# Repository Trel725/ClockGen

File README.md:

# ClockGen

## What's that?

ClockGen is a project, devoted to developing a device that allow simple synchronization of scientific equipment. When experiments require synchronization, one might select do it with Arduino or similar hardware (LabJack?) which would give millisecond accuracy, or go far beyond that to specialized timing equipment, able of generating nanosecond precise pulses and costing thousands of euro. The goal of that project is to provide "something in between", a device which can provide microsecond accuracy at reasonable price. The devise is based on STM32F446RET Nucleo development board (price below 20 euro).

## Features?

 - Generating square wave at frequencies from 610 Hz (for 16 bit timer) or 0.009 Hz (for 32 bit timer) up to ~ 10 MHz
 - Programming arbitrary sequences of start, stop or change frequency events at 1 us accuracy 
 - Support of up to 10 timer channels for generating square wave
 - Synchronization of the generated signals with nanosecond accuracy by hardware synchronization
 - Up to 22 digital outputs, programmable to generate arbitrary sequences of on/off events with 1 us accuracy and nanosecond synchronization 
 - Hardware extension for Nucleo development board, converting LVTTL signals from microcontroller (3.3V) to standard TTL (5V)
 - Add-on hardware extension, converting 5V TTL signals to high-voltage signals (7-18V).

## How to use it

```python
from clockgen import ProgramGen
from clockgen.interface import TIM, GPIO
from clockgen.utils import send_program, start_execution

#instantiate HW
tim2 = TIM("TIM2")
tim5 = TIM("TIM5")
gpa = GPIO("GPIOA")

# turn on both timers at time 100us from program start
# tim2 at 20 kHz
tim2.on_sync(20_000, 100)
# and tim5 at 10 kHz
tim5.on_sync(10_000, 100)
# start them synchnously
tim2.start_sync(100)

# set 4th and 5th pins in GPIOA to high level at 120 us
gpa.on([4, 5], 120)
# then pin 4 to low level at 150 us
gpa.off(4, 150)
# and pin 5 at 900 us
gpa.off(5, 900)

# finally turn off the timers at 1000 us
tim2.off_sync(1000)
tim5.off_sync(1000)

# instantiate program generator
pg = ProgramGen()
# and generate the program, providing it list of used HW
prog = pg.generate_program([gpa, tim2, tim5])
# open the serial connection
ser = serial.Serial("/dev/ttyACM0", baudrate=1000000, timeout=5)
# and send the program to microntroller
send_program(prog)
# and start its execution:
start_execution()
```

Also, see folder examples.

## How does it work?

1. User describes the desired sequence of operations, like start signal generation at PA0 at 300 us.
2. Host-side program keeps track of all register changes and thus translates high-level operations into low-level
register manipulation
3. Host compiles sequence of register manipilation actions into binary program for micontroller and sends the program.
4. Microcontroller stores the program in RAM and waits for the start_execution command. As soon as command is received, it starts execution and generates required sequence of signals.

## What do I need to start using the ClockGen
In the simpliest case - just STM32F446RET Nucleo development board. As soon as your equipment recognizes LVTTL (3.3V) logical levels, it should suffice. Still, majority of scientific equipment works with 5V TTL levels, and behaviour might be unpredictable if different logical levels is used, thus it is recommeded to get extension board, which converts the signals to 5V TTL. Moreover, it is capable to supply more current and electrically isolates microcontroller from high voltage spikes.

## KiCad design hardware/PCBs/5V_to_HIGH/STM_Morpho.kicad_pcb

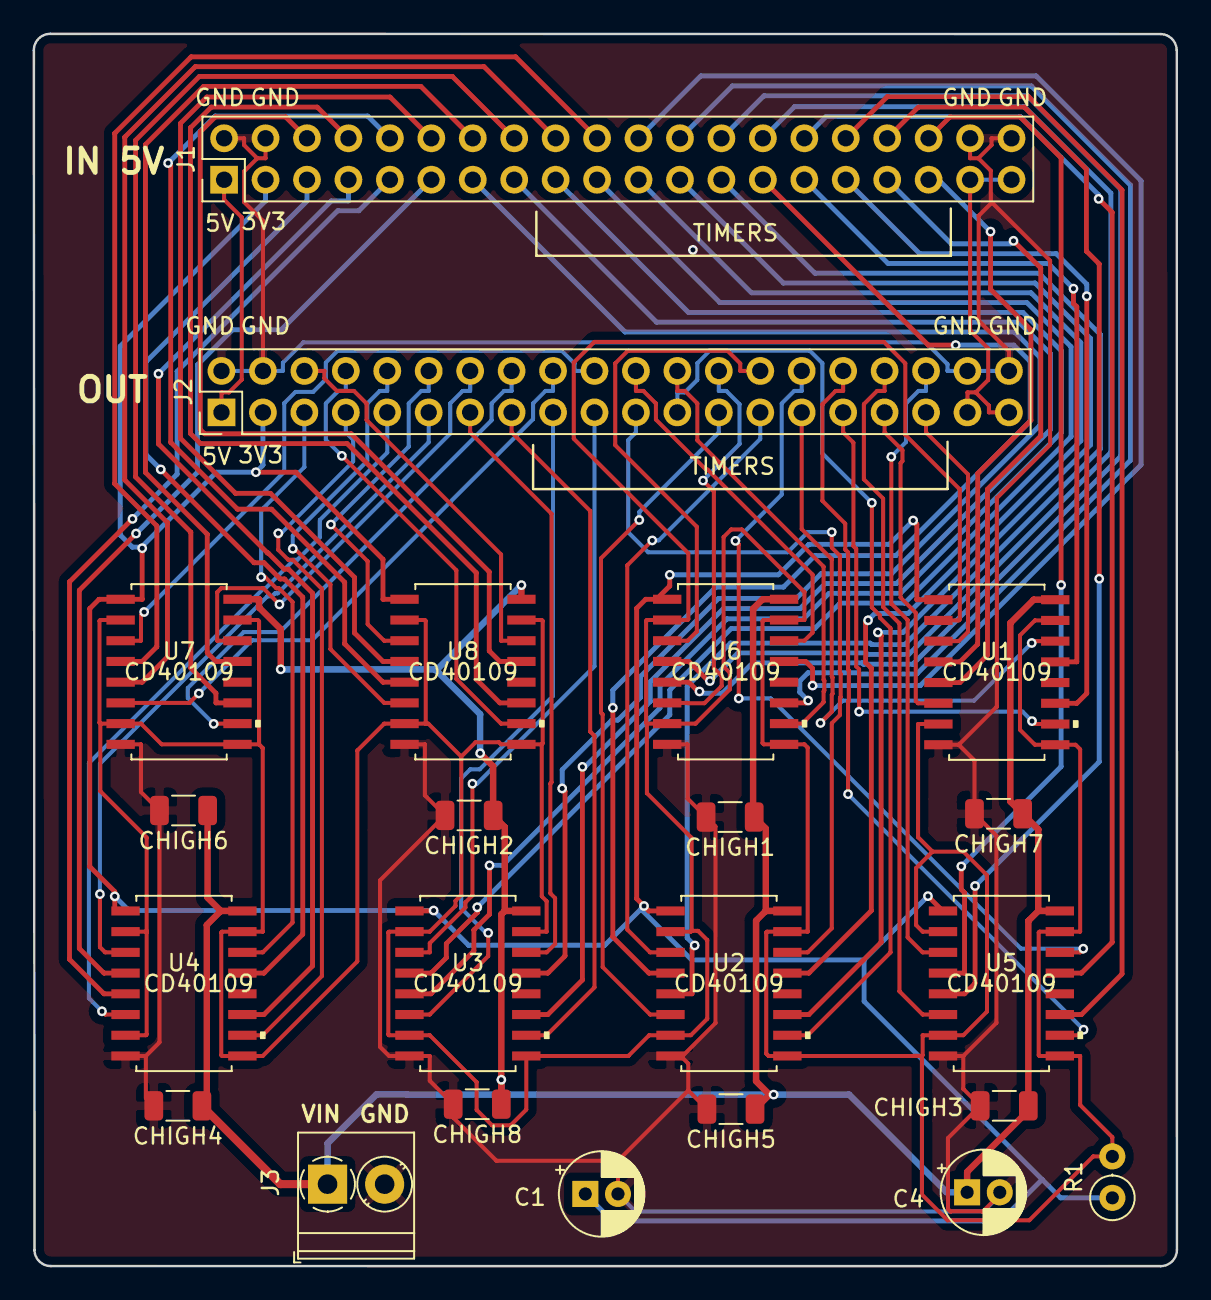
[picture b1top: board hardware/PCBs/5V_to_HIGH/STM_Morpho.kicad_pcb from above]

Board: 2 copper layers, 70.1 x 75.5 mm, 22 parts (0 on the bottom side), 70 nets.

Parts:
C1, C4: CP; CP_Radial_D5.0mm_P2.00mm
CHIGH1, CHIGH2, CHIGH3, CHIGH4, CHIGH5, CHIGH6, CHIGH7, CHIGH8: C; C_1206_3216Metric
J1, J2: Conn_02x20_Odd_Even; PinHeader_2x20_P2.54mm_Vertical
J3: Conn_01x02_Female; TerminalBlock_Phoenix_PT-1,5-2-3.5-H_1x02_P3.50mm_Horizontal
R1: 1K; R_Axial_DIN0207_L6.3mm_D2.5mm_P2.54mm_Vertical
U1, U2, U3, U4, U5, U6, U7, U8: CD40109; CD40109BNSR

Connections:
+3V3: C1.1, J1.3, J2.3, R1.1, U1.1, U2.1, U3.1, U4.1, U5.1, U6.1, U7.1, U8.1
+15V: C4.1, CHIGH1.1, CHIGH2.1, CHIGH3.1, CHIGH4.1, CHIGH5.1, CHIGH6.1, CHIGH7.1, CHIGH8.1, J3.1, U1.16, U2.16, U3.16, U4.16, U5.16, U6.16, U7.16, U8.16
/+5V: J1.1, J2.1
/NC: J1.37, J1.39, J2.37, J2.39
/PA0_5V: J2.27, U2.3
/PA0_HIGH: J1.27, U2.4
/PA1_5V: J2.15, U3.10
/PA1_HIGH: J1.15, U3.11
/PA2_5V: J2.13, U3.14
/PA2_HIGH: J1.13, U3.13
/PA3_5V: J2.11, U4.3
/PA3_HIGH: J1.11, U4.4
/PA4_5V: J2.9, U4.6
/PA4_HIGH: J1.9, U4.5
/PA5_5V: J2.7, U4.10
/PA5_HIGH: J1.7, U4.11
/PA6_5V: J2.19, U3.3
/PA6_HIGH: J1.19, U3.4
/PA7_5V: J2.17, U3.6
/PA7_HIGH: J1.17, U3.5
/PA8_5V: J2.5, U4.14
/PA8_HIGH: J1.5, U4.13
/PA9_5V: J2.36, U5.3
/PA9_HIGH: J1.36, U5.4
/PA10_5V: J2.35, U1.3
/PA10_HIGH: J1.35, U1.4
/PA11_5V: J2.34, U5.6
/PA11_HIGH: J1.34, U5.5
/PA12_5V: J2.32, U5.10
/PA12_HIGH: J1.32, U5.11
/PA13_5V: J2.30, U5.14
/PA13_HIGH: J1.30, U5.13
/PA14_5V: J2.28, U6.3
/PA14_HIGH: J1.28, U6.4
/PA15_5V: J2.26, U6.6
/PA15_HIGH: J1.26, U6.5
/PB5_5V: J2.31, U1.10
/PB5_HIGH: J1.31, U1.11
/PB6_5V: J2.29, U1.14
/PB6_HIGH: J1.29, U1.13
/PB8_5V: J2.23, U2.10
/PB8_HIGH: J1.23, U2.11
/PB9_5V: J2.21, U2.14
/PB9_HIGH: J1.21, U2.13
/PB10_5V: J2.33, U1.6
/PB10_HIGH: J1.33, U1.5
/PC0_5V: J2.24, U6.10
/PC0_HIGH: J1.24, U6.11
/PC1_5V: J2.22, U6.14
/PC1_HIGH: J1.22, U6.13
/PC2_5V: J2.20, U7.3
/PC2_HIGH: J1.20, U7.4
/PC3_5V: J2.18, U7.6
/PC3_HIGH: J1.18, U7.5
/PC4_5V: J2.16, U7.10
/PC4_HIGH: J1.16, U7.11
/PC5_5V: J2.14, U7.14
/PC5_HIGH: J1.14, U7.13
/PC6_5V: J2.12, U8.3
/PC6_HIGH: J1.12, U8.4
/PC7_5V: J2.25, U2.6
/PC7_HIGH: J1.25, U2.5
/PC8_5V: J2.10, U8.6
/PC8_HIGH: J1.10, U8.5
/PC9_5V: J2.8, U8.10
/PC9_HIGH: J1.8, U8.11
/PC10_5V: J2.6, U8.14
/PC10_HIGH: J1.6, U8.13
/PULLUP_HIGH: R1.2, U1.2, U1.7, U1.9, U1.15, U2.2, U2.7, U2.9, U2.15, U3.2, U3.7, U3.9, U3.15, U4.2, U4.7, U4.9, U4.15, U5.2, U5.7, U5.9, U5.15, U6.2, U6.7, U6.9, U6.15, U7.2, U7.7, U7.9, U7.15, U8.2, U8.7, U8.9, U8.15
GND: C1.2, C4.2, CHIGH1.2, CHIGH2.2, CHIGH3.2, CHIGH4.2, CHIGH5.2, CHIGH6.2, CHIGH7.2, CHIGH8.2, J1.2, J1.4, J1.38, J1.40, J2.2, J2.4, J2.38, J2.40, J3.2, U1.8, U2.8, U3.8, U4.8, U5.8, U6.8, U7.8, U8.8

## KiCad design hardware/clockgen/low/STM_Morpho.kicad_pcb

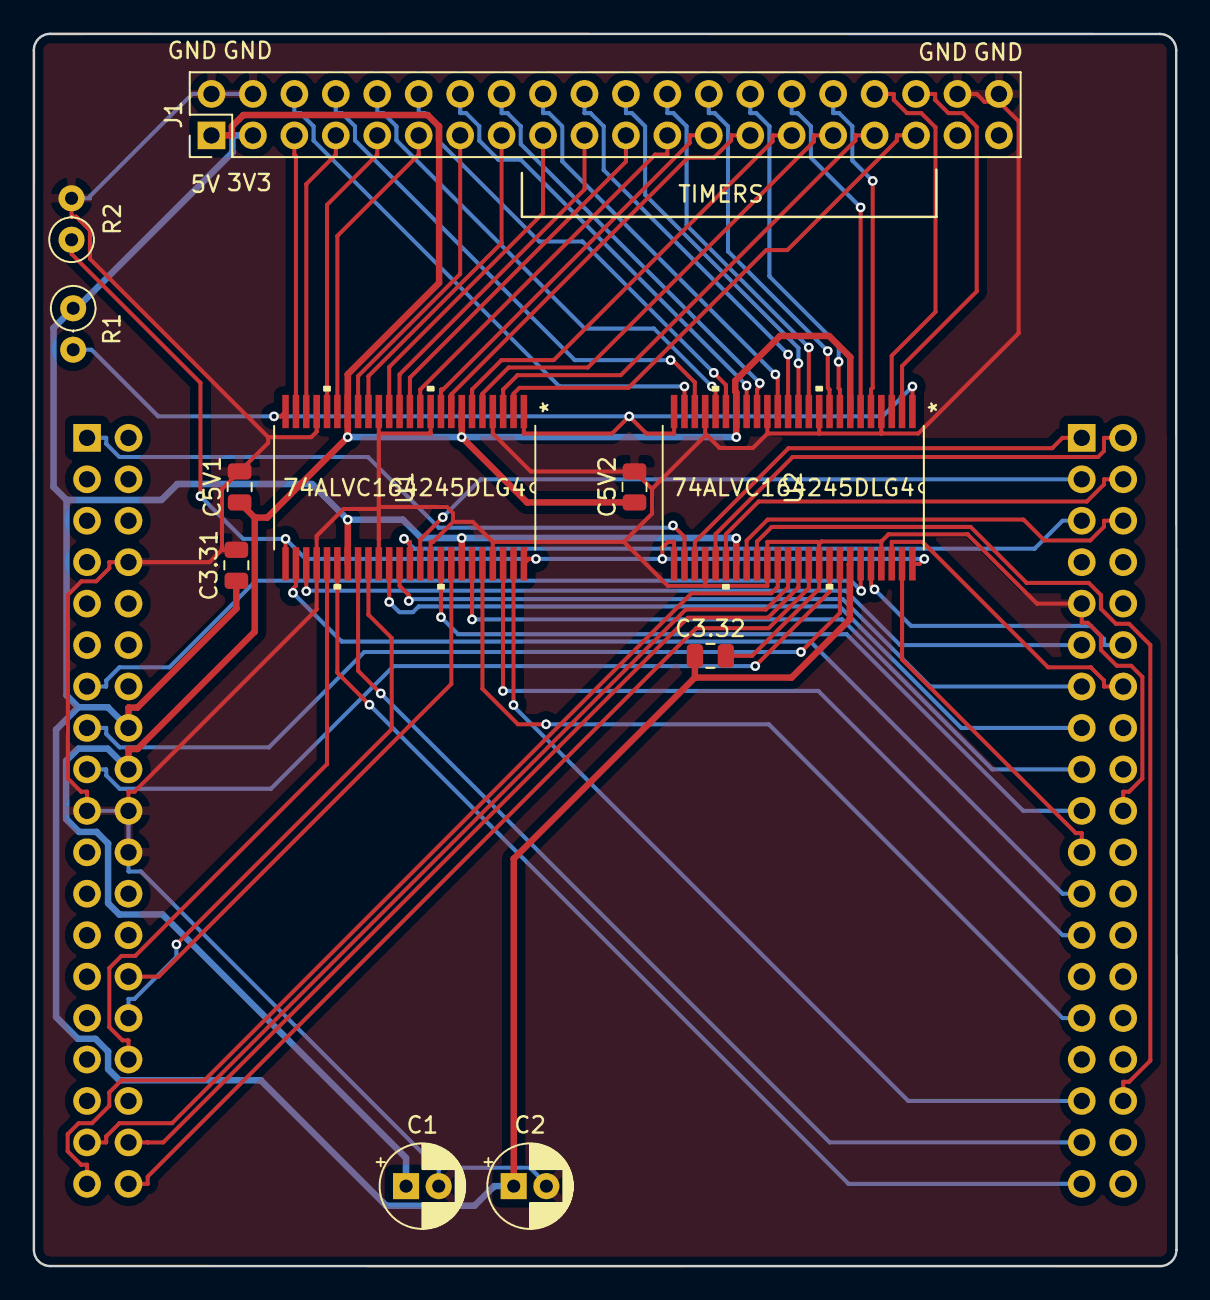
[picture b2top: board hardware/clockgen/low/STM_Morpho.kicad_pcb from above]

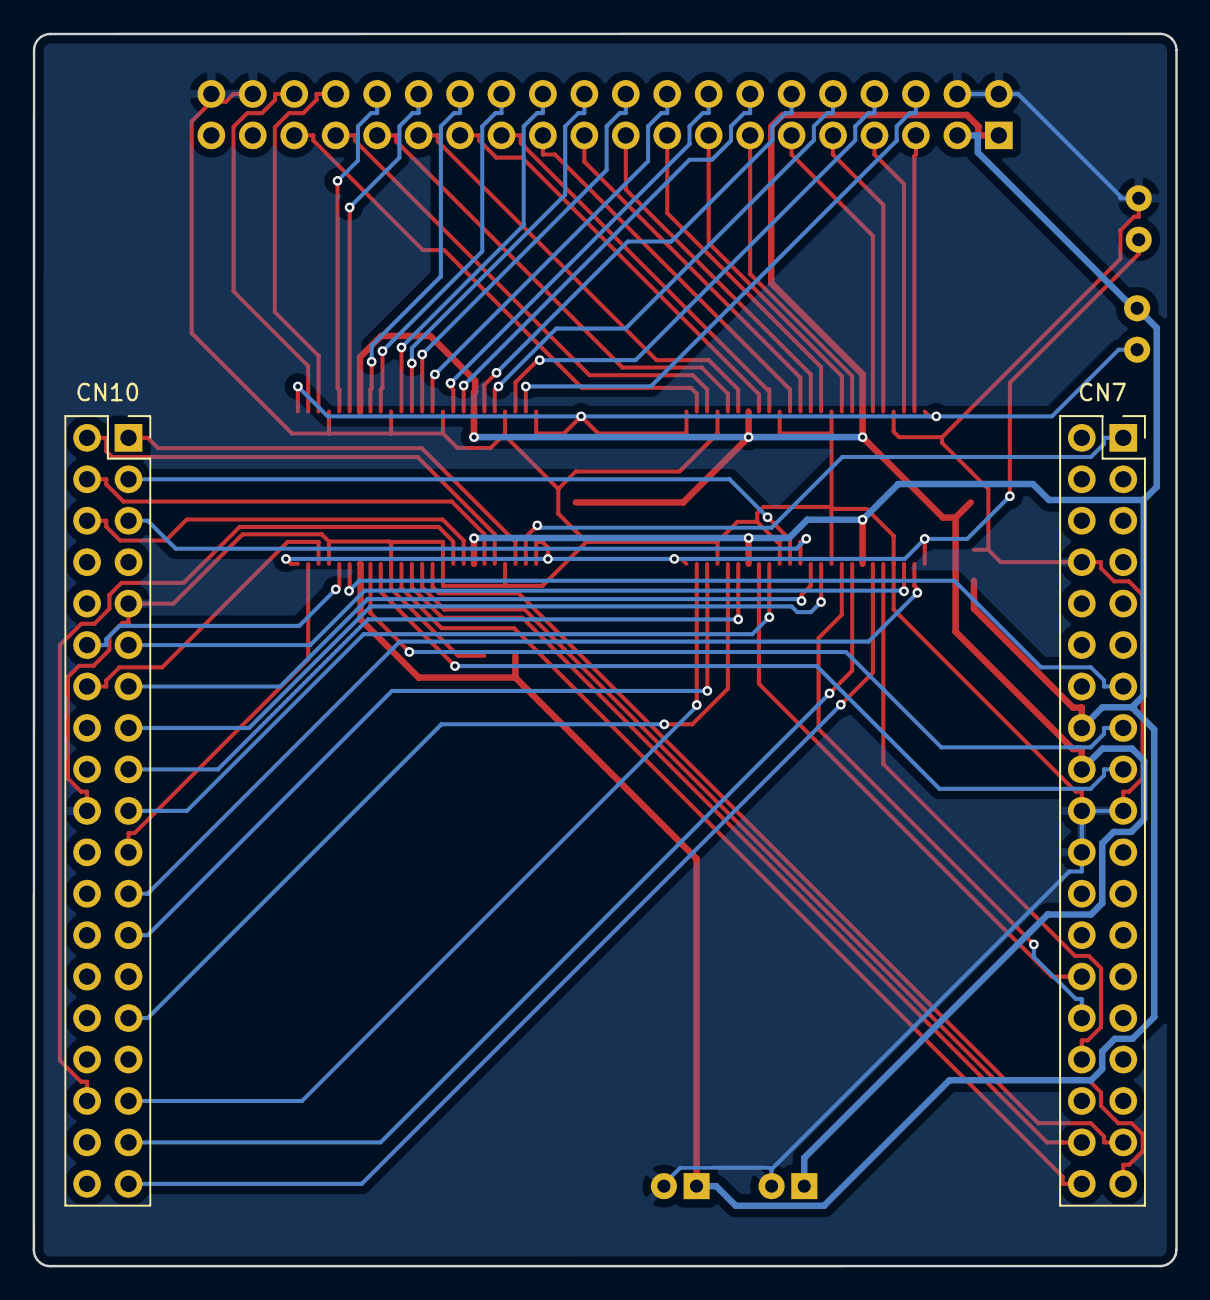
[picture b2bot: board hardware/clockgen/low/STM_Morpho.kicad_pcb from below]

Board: 2 copper layers, 70.0 x 75.5 mm, 13 parts (2 on the bottom side), 69 nets.

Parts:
C1, C2: CP; CP_Radial_D5.0mm_P2.00mm
C3.31, C3.32, C5V1, C5V2: C; C_0805_2012Metric
CN7, CN10: Conn_02x19_Odd_Even; PinSocket_2x19_P2.54mm_Vertical
J1: Conn_02x20_Odd_Even; PinHeader_2x20_P2.54mm_Vertical
R1, R2: 10K; R_Axial_DIN0207_L6.3mm_D2.5mm_P2.54mm_Vertical
U1, U2: 74ALVC164245DLG4

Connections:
+3V3: C2.1, C3.31.1, C3.32.1, CN7.16, J1.3, R1.1, U1.31, U1.42, U2.31, U2.42
+5V: C1.1, C5V1.1, C5V2.1, CN7.18, J1.1, U1.7, U1.18, U2.7, U2.18
/PA0: CN7.28, U1.41
/PA0_5V: J1.27, U1.8
/PA1: CN7.30, U1.33
/PA1_5V: J1.15, U1.16
/PA2: CN10.35, U1.32
/PA2_5V: J1.13, U1.17
/PA3: CN10.37, U1.30
/PA3_5V: J1.11, U1.19
/PA4: CN7.32, U1.29
/PA4_5V: J1.9, U1.20
/PA5: CN10.11, U1.27
/PA5_5V: J1.7, U1.22
/PA6: CN10.13, U1.36
/PA6_5V: J1.19, U1.13
/PA7: CN10.15, U1.35
/PA7_5V: J1.17, U1.14
/PA8: CN10.23, U1.26
/PA8_5V: J1.5, U1.23
/PA9: CN10.21, U2.47
/PA9_5V: J1.36, U2.2
/PA10: CN10.33, U1.47
/PA10_5V: J1.35, U1.2
/PA11: CN10.14, U2.46
/PA11_5V: J1.34, U2.3
/PA12: CN10.12, U2.44
/PA12_5V: J1.32, U2.5
/PA13: CN7.13, U2.43
/PA13_5V: J1.30, U2.6
/PA14: CN7.15, U2.41
/PA14_5V: J1.28, U2.8
/PA15: CN7.17, U2.40
/PA15_5V: J1.26, U2.9
/PB5: CN10.29, U1.44
/PB5_5V: J1.31, U1.5
/PB6: CN10.17, U1.43
/PB6_5V: J1.29, U1.6
/PB8: CN10.3, U1.38
/PB8_5V: J1.23, U1.11
/PB9: CN10.5, U1.37
/PB9_5V: J1.21, U1.12
/PB10: CN10.25, U1.46
/PB10_5V: J1.33, U1.3
/PC0: CN7.38, U2.38
/PC0_5V: J1.24, U2.11
/PC1: CN7.36, U2.37
/PC1_5V: J1.22, U2.12
/PC2: CN7.35, U2.36
/PC2_5V: J1.20, U2.13
/PC3: CN7.37, U2.35
/PC3_5V: J1.18, U2.14
/PC4: CN10.34, U2.33
/PC4_5V: J1.16, U2.16
/PC5: CN10.6, U2.32
/PC5_5V: J1.14, U2.17
/PC6: CN10.4, U2.30
/PC6_5V: J1.12, U2.19
/PC7: CN10.19, U1.40
/PC7_5V: J1.25, U1.9
/PC8: CN10.2, U2.29
/PC8_5V: J1.10, U2.20
/PC9: CN10.1, U2.27
/PC9_5V: J1.8, U2.22
/PC10: CN7.1, U2.26
/PC10_5V: J1.6, U2.23
/PULLDOWN: R2.1, U1.25, U1.48, U2.25, U2.48
/PULLUP: R1.2, U1.1, U1.24, U2.1, U2.24
GND: C1.2, C2.2, C3.31.2, C3.32.2, C5V1.2, C5V2.2, CN7.8, CN7.19, CN7.20, CN7.22, CN10.9, CN10.20, J1.2, J1.4, J1.38, J1.40, R2.2, U1.4, U1.10, U1.15, U1.21, U1.28, U1.34, U1.39, U1.45, U2.4, U2.10, U2.15, U2.21, U2.28, U2.34, U2.39, U2.45

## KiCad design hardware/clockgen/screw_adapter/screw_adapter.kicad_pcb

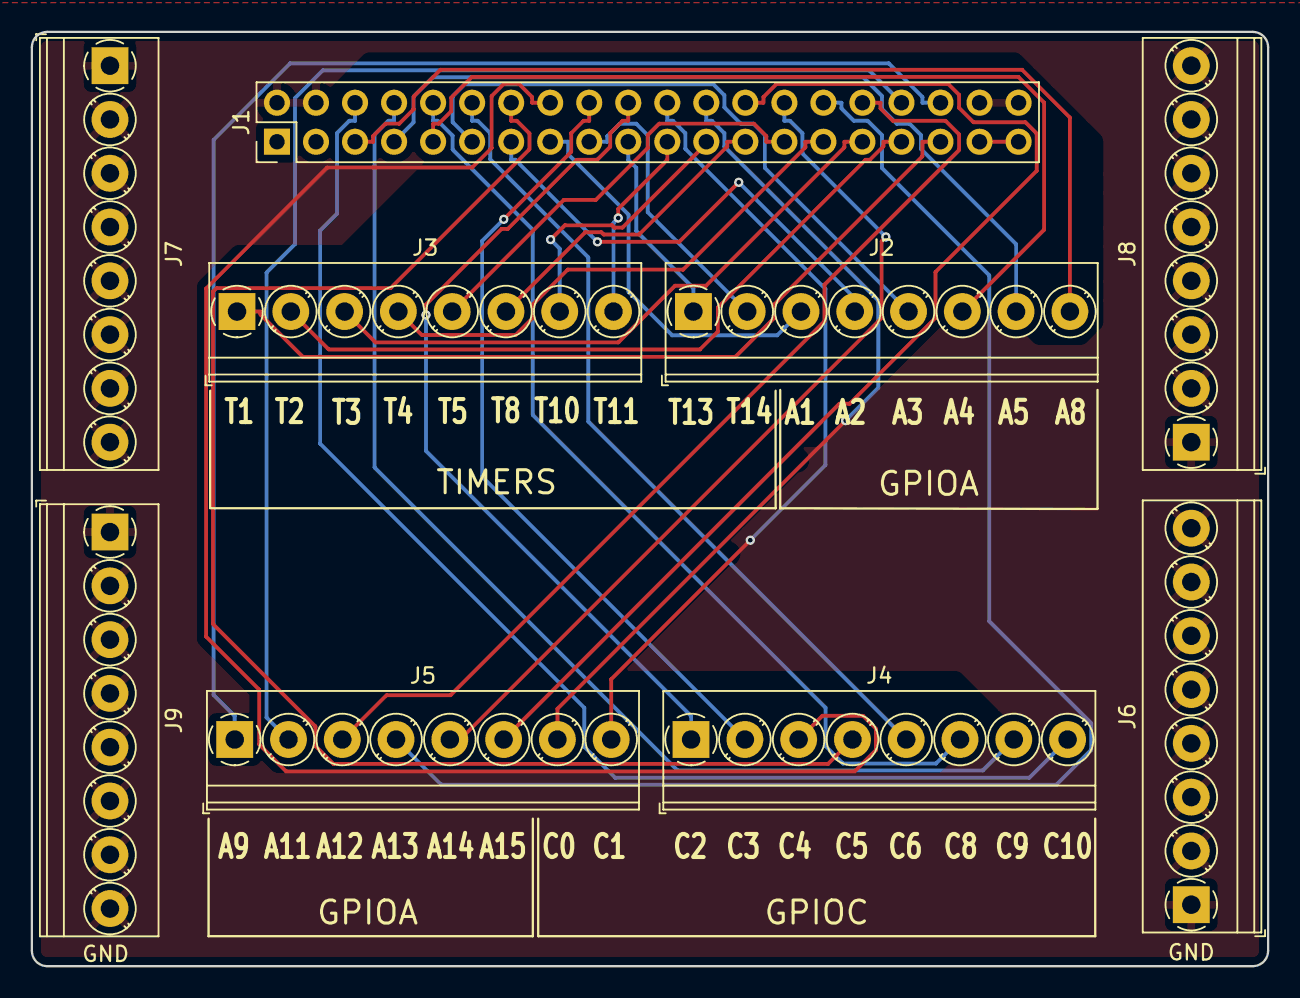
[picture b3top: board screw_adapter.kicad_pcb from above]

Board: 2 copper layers, 80.5 x 60.8 mm, 9 parts (0 on the bottom side), 34 nets.

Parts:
J1: Conn_02x20_Odd_Even; PinHeader_2x20_P2.54mm_Vertical
J2, J3, J4, J5, J6, J7, J8, J9: Screw_Terminal_01x08; TerminalBlock_Phoenix_PT-1,5-8-3.5-H_1x08_P3.50mm_Horizontal

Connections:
/NC: J1.37, J1.39
/PA0_5V: J1.27, J3.5
/PA1_5V: J1.15, J2.3
/PA2_5V: J1.13, J2.4
/PA3_5V: J1.11, J2.5
/PA4_5V: J1.9, J2.6
/PA5_5V: J1.7, J2.7
/PA6_5V: J1.19, J2.1
/PA7_5V: J1.17, J2.2
/PA8_5V: J1.5, J2.8
/PA9_5V: J1.36, J5.1
/PA10_5V: J1.35, J3.1
/PA11_5V: J1.34, J5.2
/PA12_5V: J1.32, J5.3
/PA13_5V: J1.30, J5.4
/PA14_5V: J1.28, J5.5
/PA15_5V: J1.26, J5.6
/PB5_5V: J1.31, J3.3
/PB6_5V: J1.29, J3.4
/PB8_5V: J1.23, J3.7
/PB9_5V: J1.21, J3.8
/PB10_5V: J1.33, J3.2
/PC0_5V: J1.24, J5.7
/PC1_5V: J1.22, J5.8
/PC2_5V: J1.20, J4.1
/PC3_5V: J1.18, J4.2
/PC4_5V: J1.16, J4.3
/PC5_5V: J1.14, J4.4
/PC6_5V: J1.12, J4.5
/PC7_5V: J1.25, J3.6
/PC8_5V: J1.10, J4.6
/PC9_5V: J1.8, J4.7
/PC10_5V: J1.6, J4.8
GND: J1.2, J1.4, J1.38, J1.40, J6.1, J6.2, J6.3, J6.4, J6.5, J6.6, J6.7, J6.8, J7.1, J7.2, J7.3, J7.4, J7.5, J7.6, J7.7, J7.8, J8.1, J8.2, J8.3, J8.4, J8.5, J8.6, J8.7, J8.8, J9.1, J9.2, J9.3, J9.4, J9.5, J9.6, J9.7, J9.8

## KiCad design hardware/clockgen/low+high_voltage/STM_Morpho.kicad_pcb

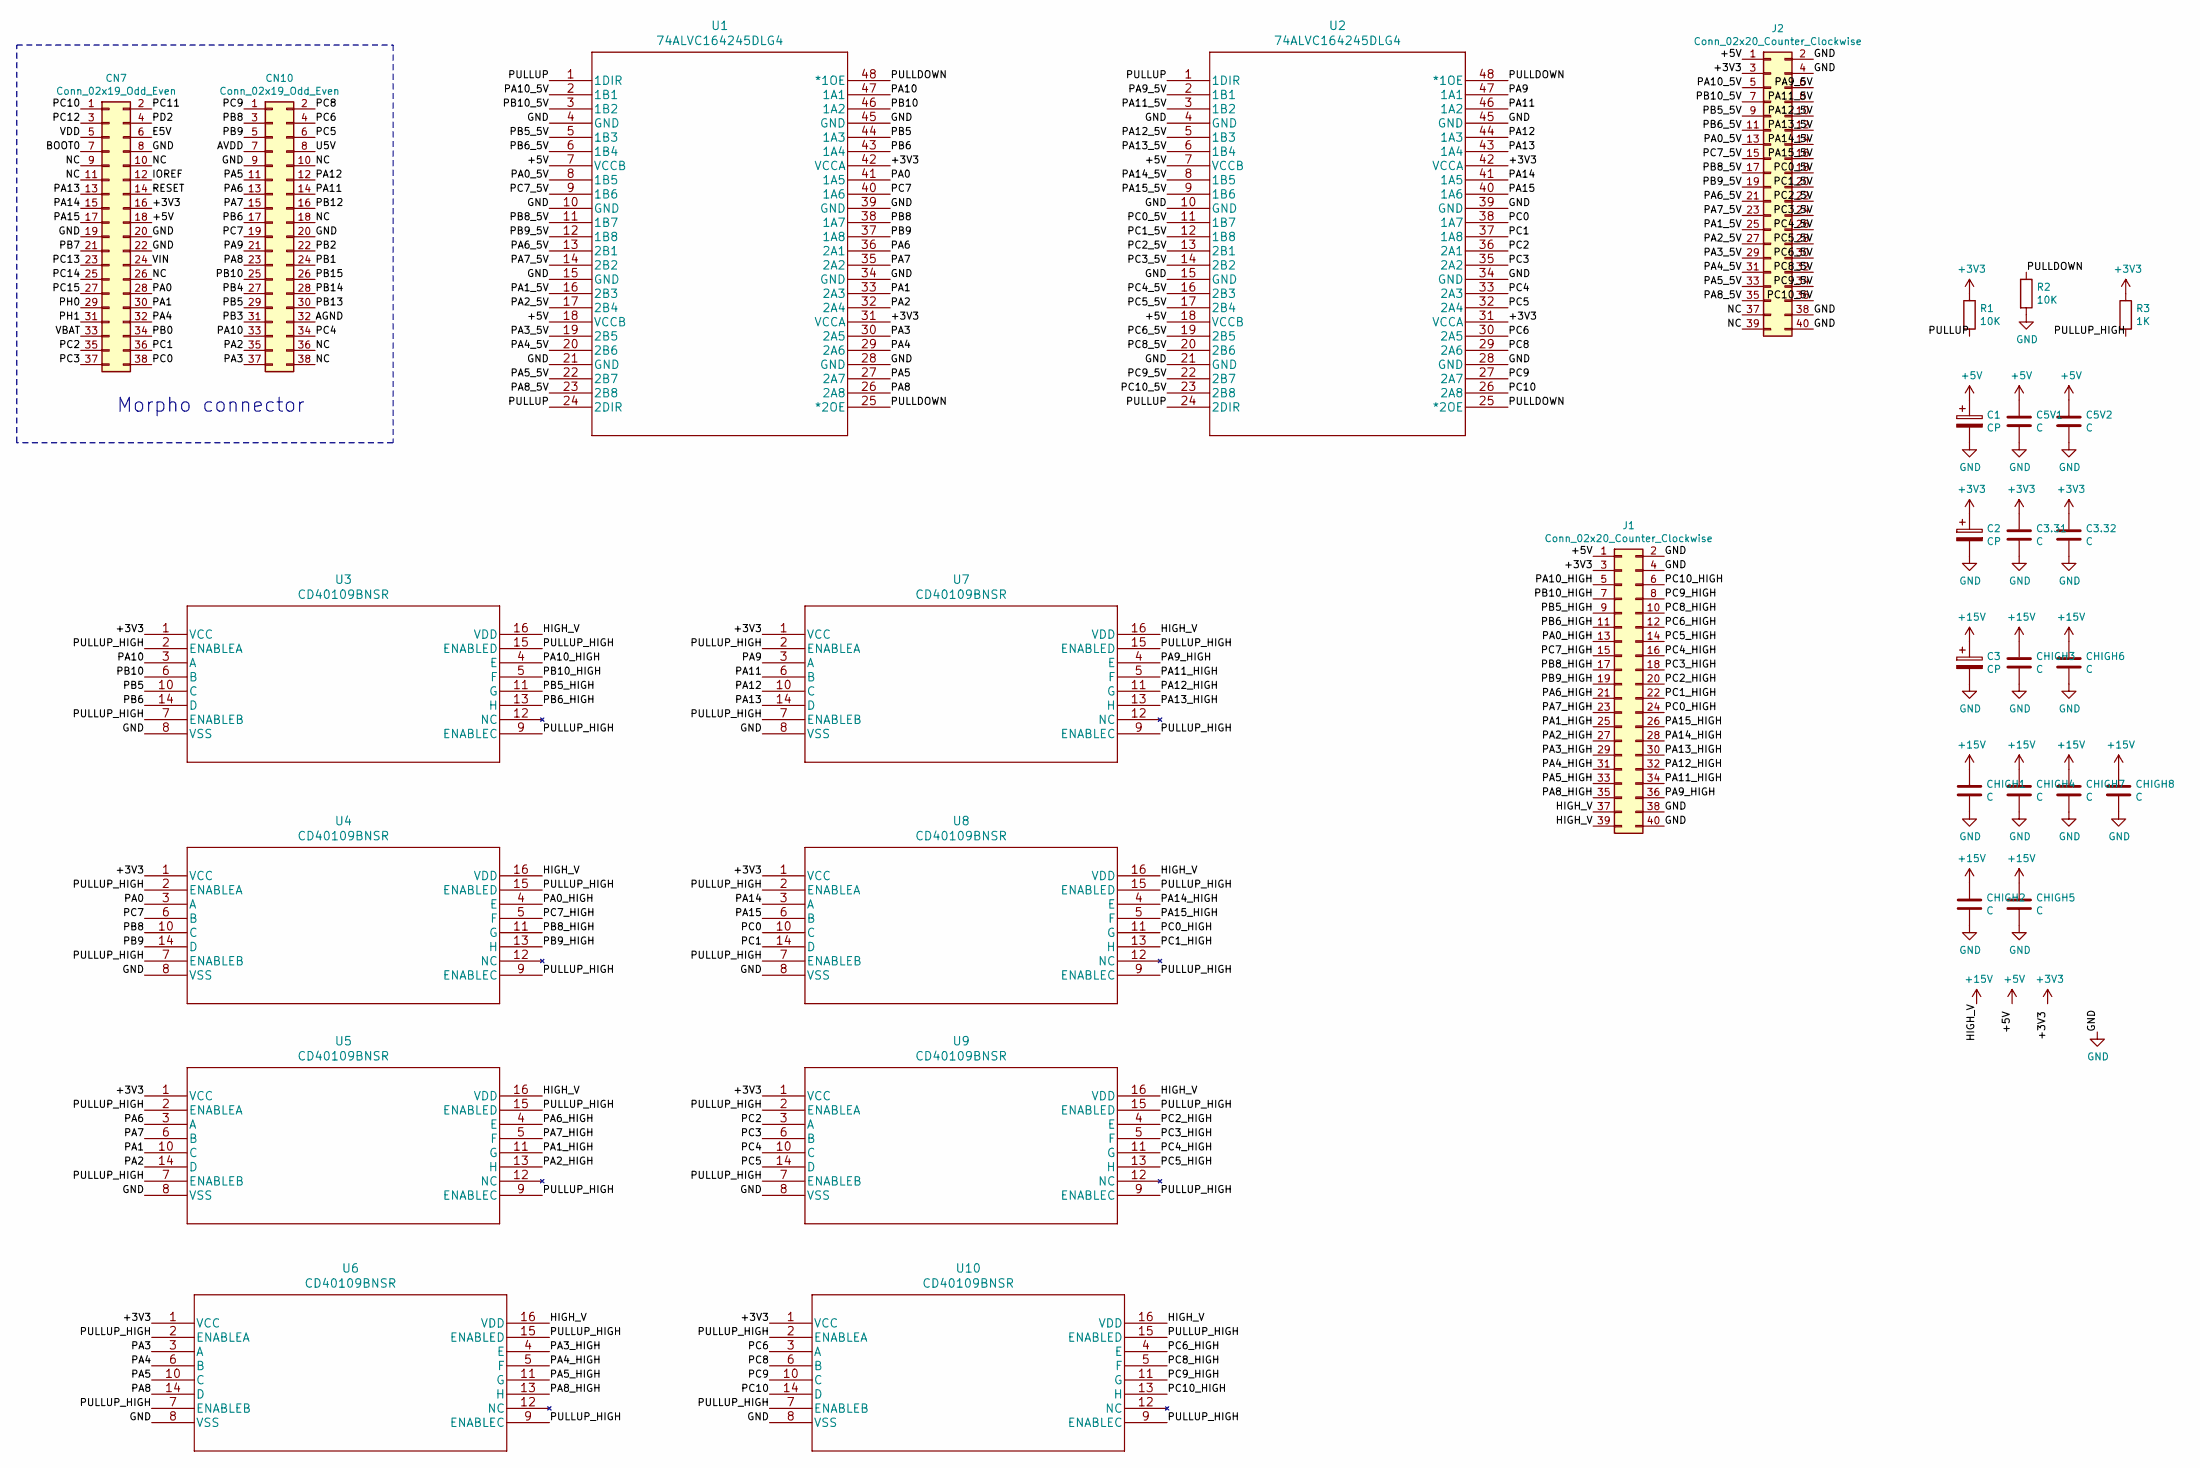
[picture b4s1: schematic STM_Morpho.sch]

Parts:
C1, C2, C3: CP; CP_Radial_D5.0mm_P2.00mm
C3.31, C3.32, C5V1, C5V2: C; C_0805_2012Metric
CHIGH1, CHIGH2, CHIGH3, CHIGH4, CHIGH5, CHIGH6, CHIGH7, CHIGH8: C; C_1206_3216Metric
CN7, CN10: Conn_02x19_Odd_Even; PinSocket_2x19_P2.54mm_Vertical
J1, J2: Conn_02x20_Counter_Clockwise; PinHeader_2x20_P2.54mm_Vertical
R1, R2: 10K; R_Axial_DIN0207_L6.3mm_D2.5mm_P2.54mm_Vertical
R3: 1K; R_Axial_DIN0207_L6.3mm_D2.5mm_P2.54mm_Vertical
U1, U2: 74ALVC164245DLG4
U3, U4, U5, U6, U7, U8, U9, U10: CD40109BNSR

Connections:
+3V3: C2.1, C3.31.1, C3.32.1, CN7.16, J1.3, J2.3, R1.1, R3.1, U1.31 (VCCA), U1.42 (VCCA), U2.31 (VCCA), U2.42 (VCCA), U3.1 (VCC), U4.1 (VCC), U5.1 (VCC), U6.1 (VCC), U7.1 (VCC), U8.1 (VCC), U9.1 (VCC), U10.1 (VCC)
+5V: C1.1, C5V1.1, C5V2.1, CN7.18, J1.1, J2.1, U1.7 (VCCB), U1.18 (VCCB), U2.7 (VCCB), U2.18 (VCCB)
+15V: C3.1, CHIGH1.1, CHIGH2.1, CHIGH3.1, CHIGH4.1, CHIGH5.1, CHIGH6.1, CHIGH7.1, CHIGH8.1, J1.37, J1.39, U3.16 (VDD), U4.16 (VDD), U5.16 (VDD), U6.16 (VDD), U7.16 (VDD), U8.16 (VDD), U9.16 (VDD), U10.16 (VDD)
/AGND: CN10.32
/AVDD: CN10.7
/BOOT0: CN7.7
/E5V: CN7.6
/IOREF: CN7.12
/NC: CN7.9, CN7.10, CN7.11, CN7.26, CN10.10, CN10.18, CN10.36, CN10.38, J2.37, J2.39
/PA0: CN7.28, U1.41 (1A5), U4.3 (A)
/PA0_5V: J2.13, U1.8 (1B5)
/PA0_HIGH: J1.13, U4.4 (E)
/PA1: CN7.30, U1.33 (2A3), U5.10 (C)
/PA1_5V: J2.25, U1.16 (2B3)
/PA1_HIGH: J1.25, U5.11 (G)
/PA2: CN10.35, U1.32 (2A4), U5.14 (D)
/PA2_5V: J2.27, U1.17 (2B4)
/PA2_HIGH: J1.27, U5.13 (H)
/PA3: CN10.37, U1.30 (2A5), U6.3 (A)
/PA3_5V: J2.29, U1.19 (2B5)
/PA3_HIGH: J1.29, U6.4 (E)
/PA4: CN7.32, U1.29 (2A6), U6.6 (B)
/PA4_5V: J2.31, U1.20 (2B6)
/PA4_HIGH: J1.31, U6.5 (F)
/PA5: CN10.11, U1.27 (2A7), U6.10 (C)
/PA5_5V: J2.33, U1.22 (2B7)
/PA5_HIGH: J1.33, U6.11 (G)
/PA6: CN10.13, U1.36 (2A1), U5.3 (A)
/PA6_5V: J2.21, U1.13 (2B1)
/PA6_HIGH: J1.21, U5.4 (E)
/PA7: CN10.15, U1.35 (2A2), U5.6 (B)
/PA7_5V: J2.23, U1.14 (2B2)
/PA7_HIGH: J1.23, U5.5 (F)
/PA8: CN10.23, U1.26 (2A8), U6.14 (D)
/PA8_5V: J2.35, U1.23 (2B8)
/PA8_HIGH: J1.35, U6.13 (H)
/PA9: CN10.21, U2.47 (1A1), U7.3 (A)
/PA9_5V: J2.6, U2.2 (1B1)
/PA9_HIGH: J1.36, U7.4 (E)
/PA10: CN10.33, U1.47 (1A1), U3.3 (A)
/PA10_5V: J2.5, U1.2 (1B1)
/PA10_HIGH: J1.5, U3.4 (E)
/PA11: CN10.14, U2.46 (1A2), U7.6 (B)
/PA11_5V: J2.8, U2.3 (1B2)
/PA11_HIGH: J1.34, U7.5 (F)
/PA12: CN10.12, U2.44 (1A3), U7.10 (C)
/PA12_5V: J2.10, U2.5 (1B3)
/PA12_HIGH: J1.32, U7.11 (G)
/PA13: CN7.13, U2.43 (1A4), U7.14 (D)
/PA13_5V: J2.12, U2.6 (1B4)
/PA13_HIGH: J1.30, U7.13 (H)
/PA14: CN7.15, U2.41 (1A5), U8.3 (A)
/PA14_5V: J2.14, U2.8 (1B5)
/PA14_HIGH: J1.28, U8.4 (E)
/PA15: CN7.17, U2.40 (1A6), U8.6 (B)
/PA15_5V: J2.16, U2.9 (1B6)
/PA15_HIGH: J1.26, U8.5 (F)
/PB0: CN7.34
/PB1: CN10.24
/PB2: CN10.22
/PB3: CN10.31
/PB4: CN10.27
/PB5: CN10.29, U1.44 (1A3), U3.10 (C)
/PB5_5V: J2.9, U1.5 (1B3)
/PB5_HIGH: J1.9, U3.11 (G)
/PB6: CN10.17, U1.43 (1A4), U3.14 (D)
/PB6_5V: J2.11, U1.6 (1B4)
/PB6_HIGH: J1.11, U3.13 (H)
/PB7: CN7.21
/PB8: CN10.3, U1.38 (1A7), U4.10 (C)
/PB8_5V: J2.17, U1.11 (1B7)
/PB8_HIGH: J1.17, U4.11 (G)
/PB9: CN10.5, U1.37 (1A8), U4.14 (D)
/PB9_5V: J2.19, U1.12 (1B8)
/PB9_HIGH: J1.19, U4.13 (H)
/PB10: CN10.25, U1.46 (1A2), U3.6 (B)
/PB10_5V: J2.7, U1.3 (1B2)
/PB10_HIGH: J1.7, U3.5 (F)
/PB12: CN10.16
/PB13: CN10.30
/PB14: CN10.28
/PB15: CN10.26
/PC0: CN7.38, U2.38 (1A7), U8.10 (C)
/PC0_5V: J2.18, U2.11 (1B7)
/PC0_HIGH: J1.24, U8.11 (G)
/PC1: CN7.36, U2.37 (1A8), U8.14 (D)
/PC1_5V: J2.20, U2.12 (1B8)
/PC1_HIGH: J1.22, U8.13 (H)
/PC2: CN7.35, U2.36 (2A1), U9.3 (A)
/PC2_5V: J2.22, U2.13 (2B1)
/PC2_HIGH: J1.20, U9.4 (E)
/PC3: CN7.37, U2.35 (2A2), U9.6 (B)
/PC3_5V: J2.24, U2.14 (2B2)
/PC3_HIGH: J1.18, U9.5 (F)
/PC4: CN10.34, U2.33 (2A3), U9.10 (C)
/PC4_5V: J2.26, U2.16 (2B3)
/PC4_HIGH: J1.16, U9.11 (G)
/PC5: CN10.6, U2.32 (2A4), U9.14 (D)
/PC5_5V: J2.28, U2.17 (2B4)
/PC5_HIGH: J1.14, U9.13 (H)
/PC6: CN10.4, U2.30 (2A5), U10.3 (A)
/PC6_5V: J2.30, U2.19 (2B5)
/PC6_HIGH: J1.12, U10.4 (E)
/PC7: CN10.19, U1.40 (1A6), U4.6 (B)
/PC7_5V: J2.15, U1.9 (1B6)
/PC7_HIGH: J1.15, U4.5 (F)
/PC8: CN10.2, U2.29 (2A6), U10.6 (B)
/PC8_5V: J2.32, U2.20 (2B6)
/PC8_HIGH: J1.10, U10.5 (F)
/PC9: CN10.1, U2.27 (2A7), U10.10 (C)
/PC9_5V: J2.34, U2.22 (2B7)
/PC9_HIGH: J1.8, U10.11 (G)
/PC10: CN7.1, U2.26 (2A8), U10.14 (D)
/PC10_5V: J2.36, U2.23 (2B8)
/PC10_HIGH: J1.6, U10.13 (H)
/PC11: CN7.2
/PC12: CN7.3
/PC13: CN7.23
/PC14: CN7.25
/PC15: CN7.27
/PD2: CN7.4
/PH0: CN7.29
/PH1: CN7.31
/PULLDOWN: R2.1, U1.25 (*2OE), U1.48 (*1OE), U2.25 (*2OE), U2.48 (*1OE)
/PULLUP: R1.2, U1.1 (1DIR), U1.24 (2DIR), U2.1 (1DIR), U2.24 (2DIR)
/PULLUP_HIGH: R3.2, U3.2 (ENABLEA), U3.7 (ENABLEB), U3.9 (ENABLEC), U3.15 (ENABLED), U4.2 (ENABLEA), U4.7 (ENABLEB), U4.9 (ENABLEC), U4.15 (ENABLED), U5.2 (ENABLEA), U5.7 (ENABLEB), U5.9 (ENABLEC), U5.15 (ENABLED), U6.2 (ENABLEA), U6.7 (ENABLEB), U6.9 (ENABLEC), U6.15 (ENABLED), U7.2 (ENABLEA), U7.7 (ENABLEB), U7.9 (ENABLEC), U7.15 (ENABLED), U8.2 (ENABLEA), U8.7 (ENABLEB), U8.9 (ENABLEC), U8.15 (ENABLED), U9.2 (ENABLEA), U9.7 (ENABLEB), U9.9 (ENABLEC), U9.15 (ENABLED), U10.2 (ENABLEA), U10.7 (ENABLEB), U10.9 (ENABLEC), U10.15 (ENABLED)
/RESET: CN7.14
/U5V: CN10.8
/VBAT: CN7.33
/VDD: CN7.5
/VIN: CN7.24
GND: C1.2, C2.2, C3.2, C3.31.2, C3.32.2, C5V1.2, C5V2.2, CHIGH1.2, CHIGH2.2, CHIGH3.2, CHIGH4.2, CHIGH5.2, CHIGH6.2, CHIGH7.2, CHIGH8.2, CN7.8, CN7.19, CN7.20, CN7.22, CN10.9, CN10.20, J1.2, J1.4, J1.38, J1.40, J2.2, J2.4, J2.38, J2.40, R2.2, U1.4 (GND), U1.10 (GND), U1.15 (GND), U1.21 (GND), U1.28 (GND), U1.34 (GND), U1.39 (GND), U1.45 (GND), U2.4 (GND), U2.10 (GND), U2.15 (GND), U2.21 (GND), U2.28 (GND), U2.34 (GND), U2.39 (GND), U2.45 (GND), U3.8 (VSS), U4.8 (VSS), U5.8 (VSS), U6.8 (VSS), U7.8 (VSS), U8.8 (VSS), U9.8 (VSS), U10.8 (VSS)

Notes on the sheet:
Morpho connector

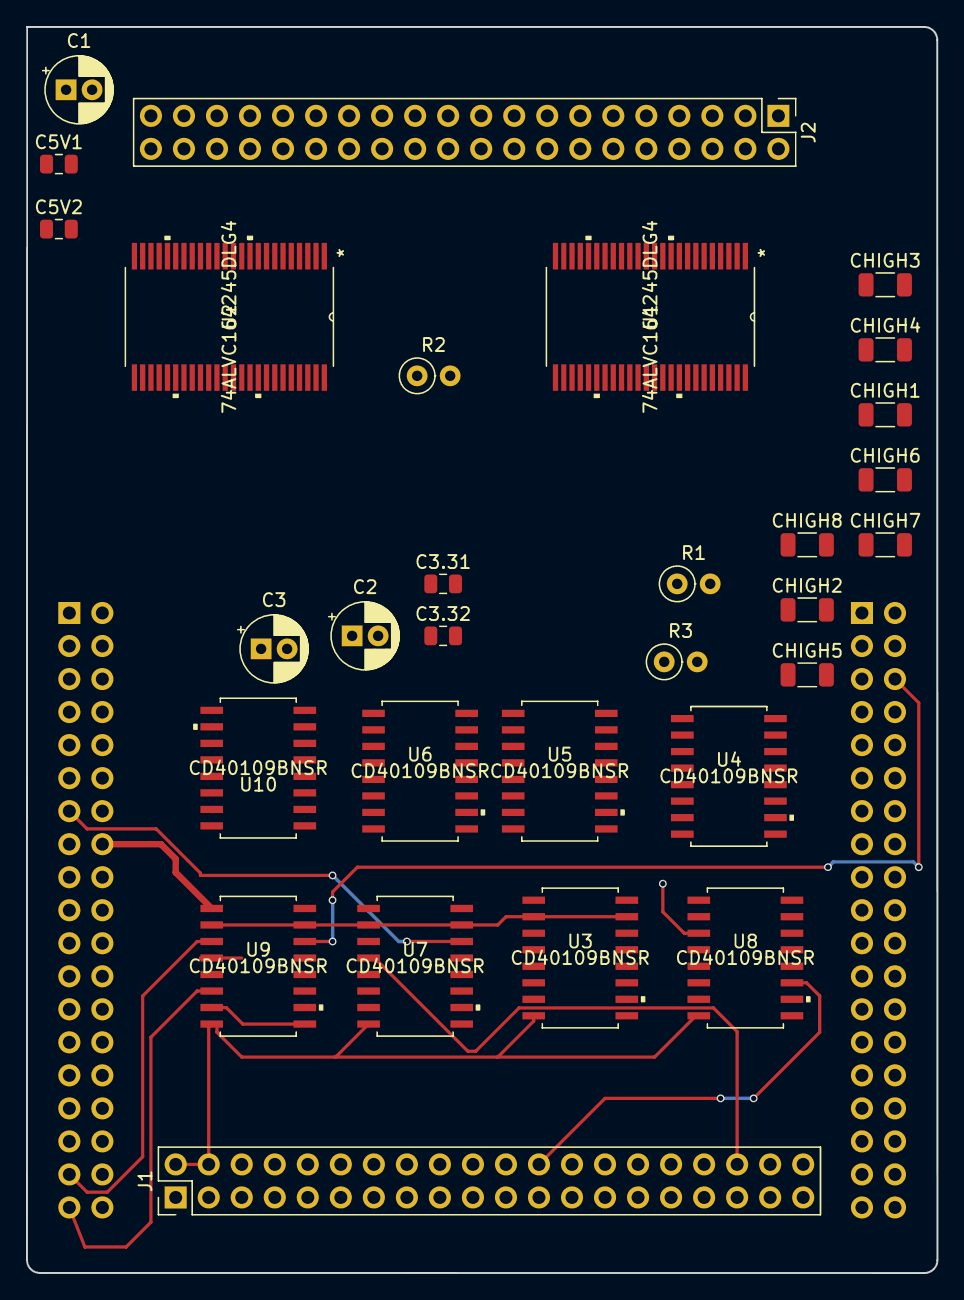
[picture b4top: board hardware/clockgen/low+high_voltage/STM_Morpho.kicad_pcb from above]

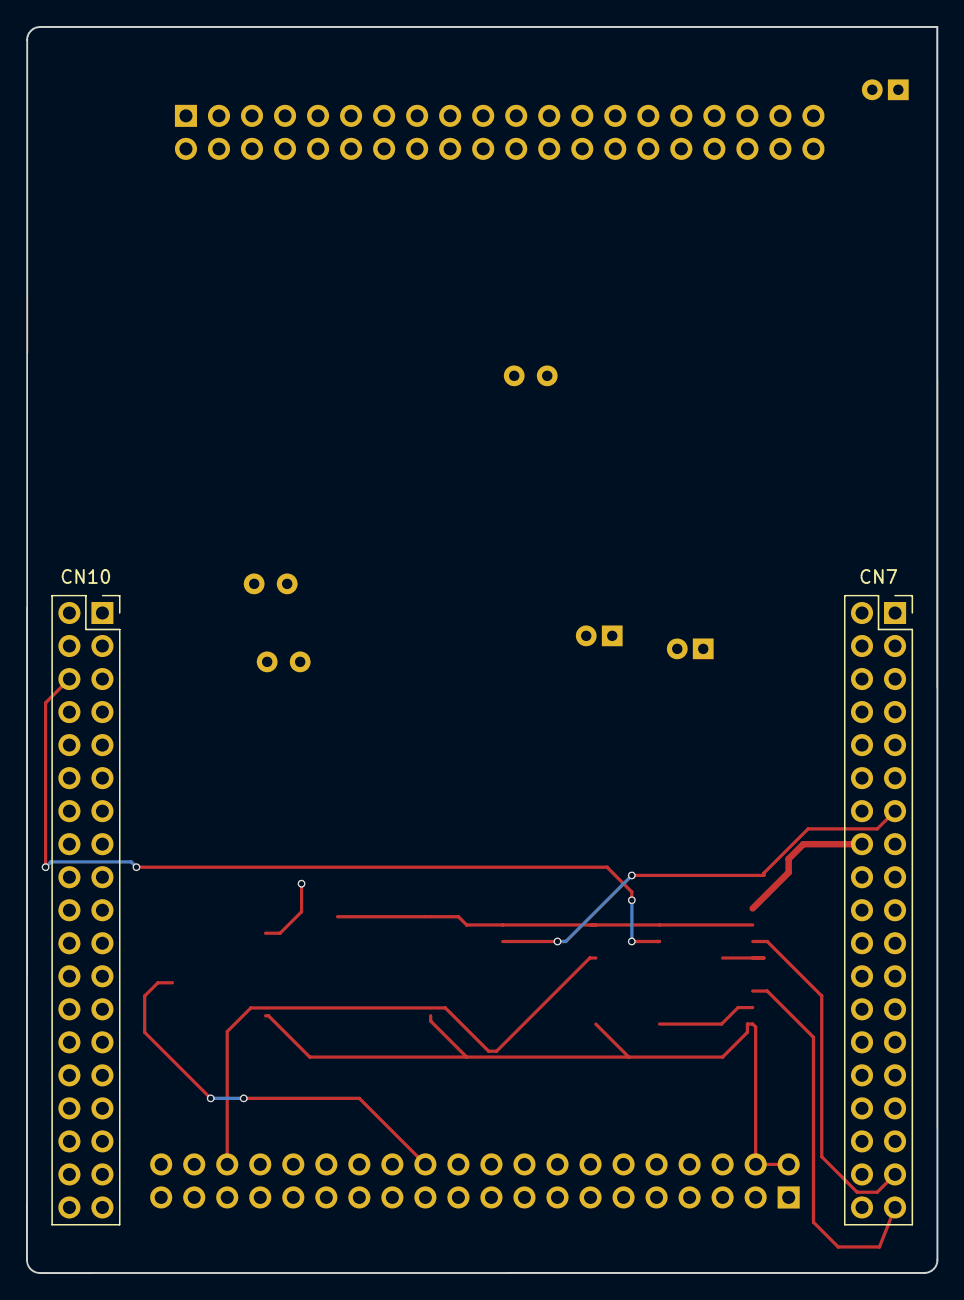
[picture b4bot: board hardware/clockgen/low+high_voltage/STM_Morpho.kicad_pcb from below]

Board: 4 copper layers, 70.0 x 95.8 mm, 32 parts (2 on the bottom side), 104 nets.

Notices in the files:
firmware/Core/Src/stm32f4xx_hal_msp.c:
© Copyright (c) 2021 STMicroelectronics.
All rights reserved.
This software component is licensed by ST under BSD 3-Clause license,
the "License"; You may not use this file except in compliance with the
License. You may obtain a copy of the License at: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
(C) COPYRIGHT STMicroelectronics *****END OF FILE
parts and their libraries:
Copyright 2021 Accelerated Designs. All rights reserved.
